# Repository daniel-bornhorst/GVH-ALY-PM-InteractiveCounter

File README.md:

# GVH-ALY-PM-InteractiveCounter

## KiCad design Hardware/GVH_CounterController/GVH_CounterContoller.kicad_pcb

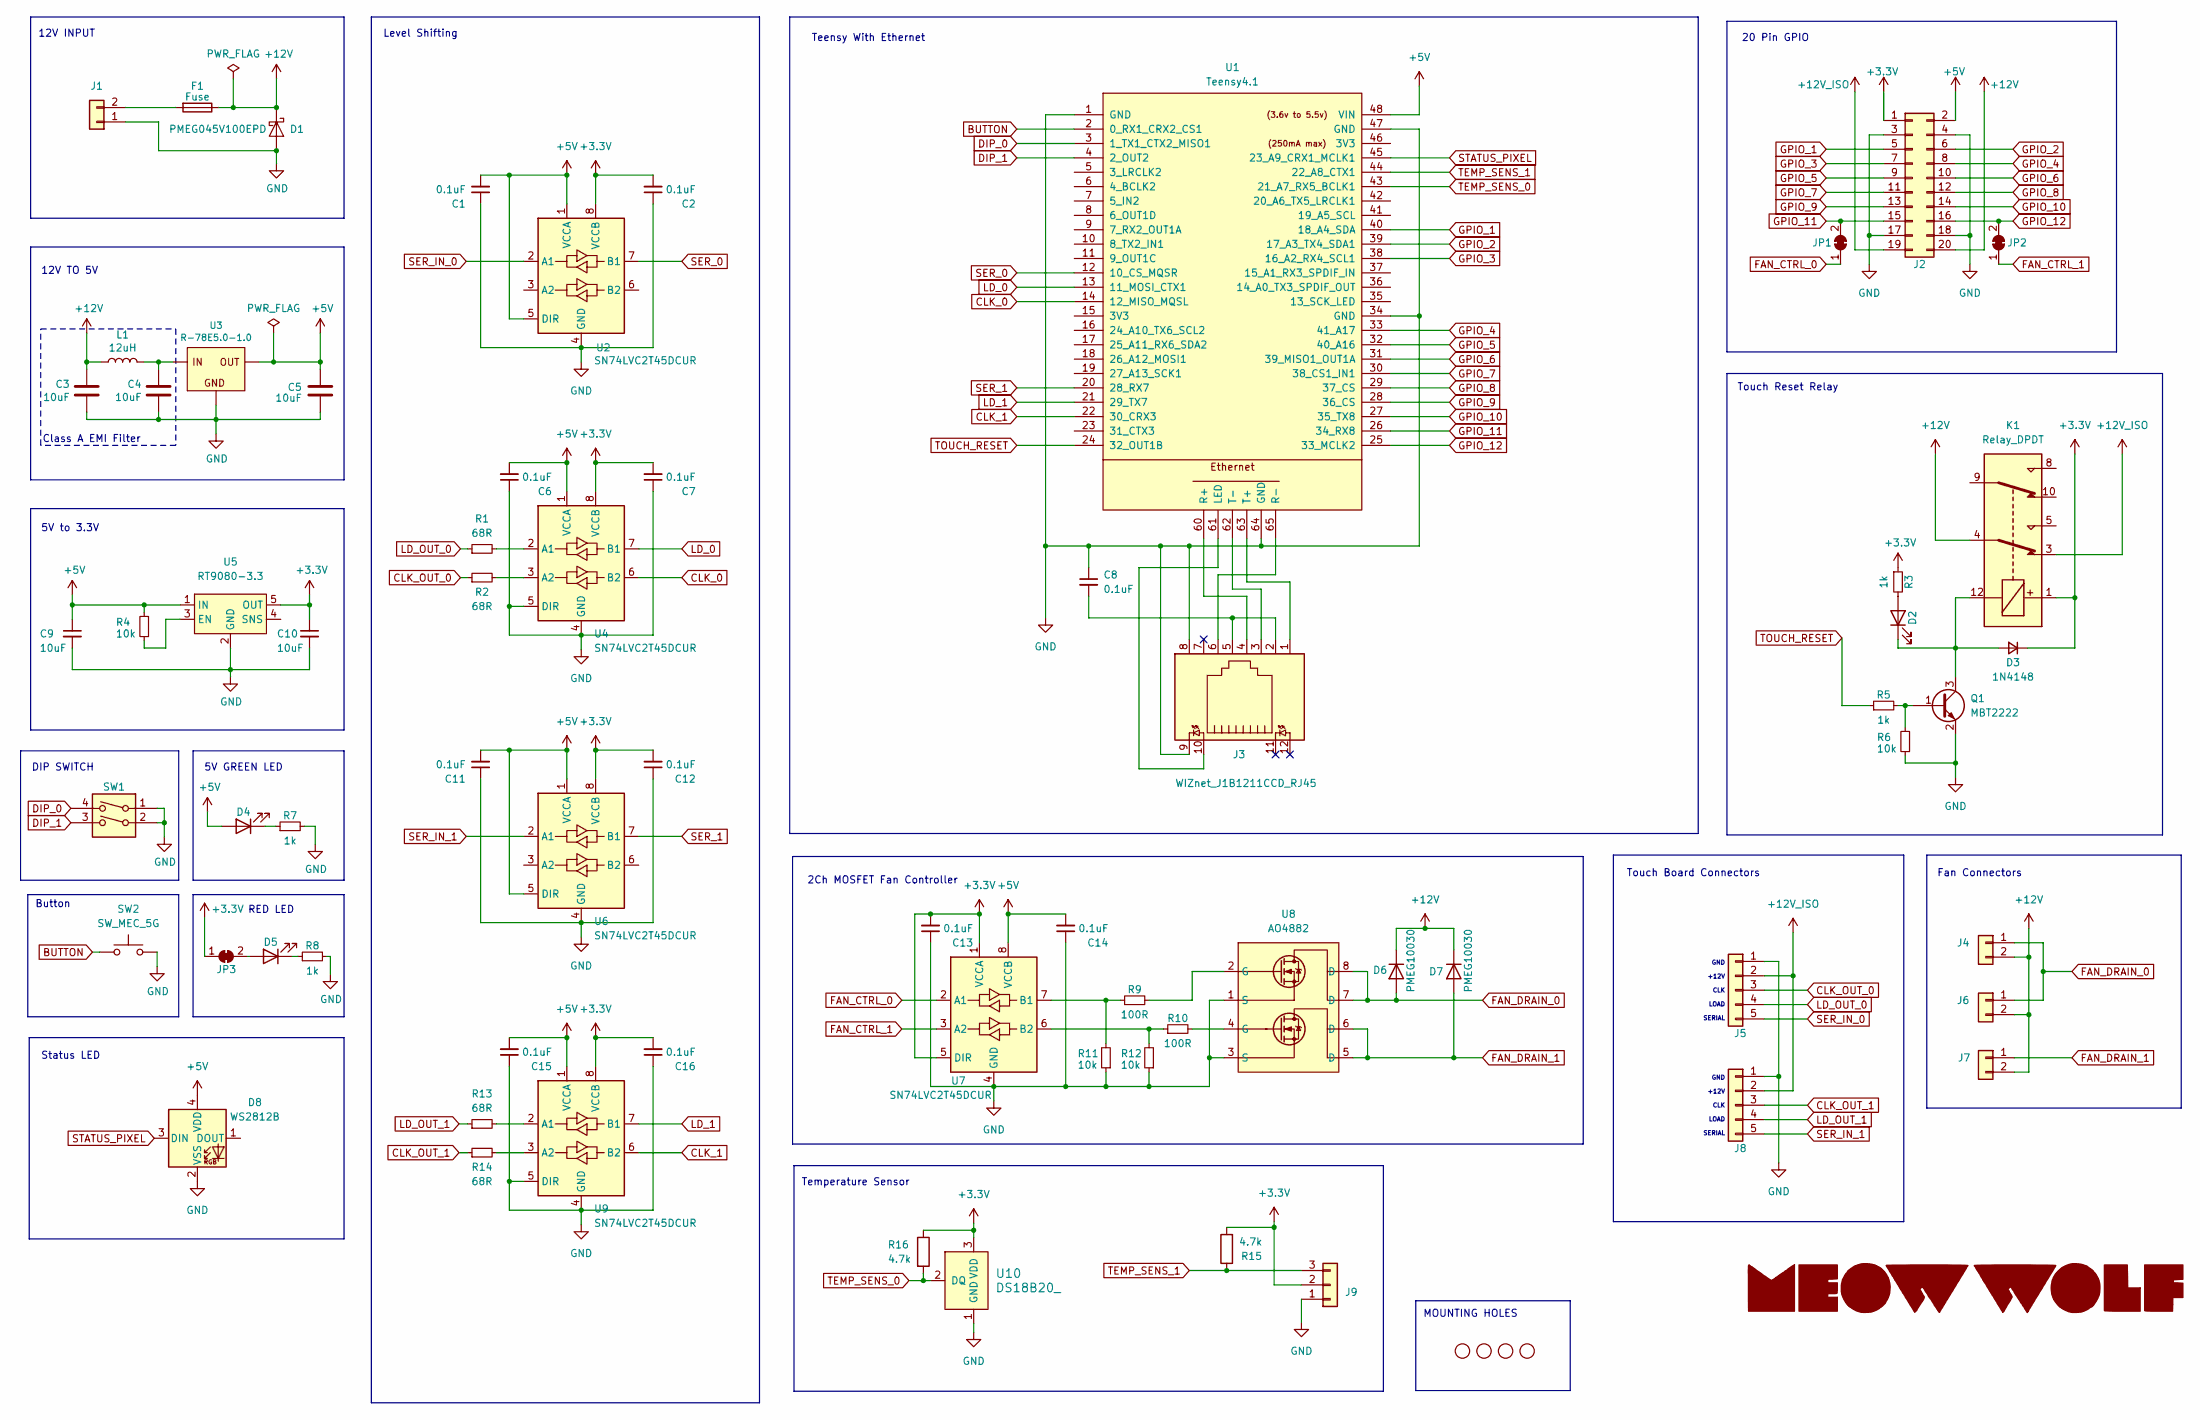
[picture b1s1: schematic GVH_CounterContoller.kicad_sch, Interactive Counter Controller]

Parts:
C1, C2, C6, C7, C11, C12, C13, C14, C15, C16: 0.1uF; C_0402_1005Metric; LCSC C1525
C3, C4, C5: 10uF; C_1206_3216Metric; Digikey P/N 1276-6767-1-ND
C8: 0.1uF; C_0805_2012Metric; LCSC C1711
C9, C10: 10uF; C_0805_2012Metric; LCSC C15850
D1: PMEG045V100EPD; Nexperia_CFP15_SOT-1289; LCSC C5183016
D2, D5: RED LED; LED_0603_1608Metric; Digikey P/N LTST-C190KRKT
D3: 1N4148; D_SOD-323; Digikey P/N 1N4148WS-FDICT-ND
D4: GREEN LED; LED_0603_1608Metric; Digikey P/N 160-1888-1-ND
D6, D7: PMEG10030; D_SOD-128; LCSC C5260346
D8: WS2812B; LED_WS2812B-2020_PLCC4_2.0x2.0mm; LCSC C965555
F1: Fuse; Fuseholder_2AG_5x15mm_Littelfuse_01110501Z; Digikey P/N F4189-ND
H1, H2, H3, H4: STAND-OFF
J1: Molex Ultra-Fit; MOLEX_ULTRAFIT-RA-2POS_1723104102; Digikey P/N 900-1723104102-ND
J2: Vertical Header Pins; PinHeader_2x10_P2.54mm_Vertical; Digikey P/N 2057-PH2-20-UA-ND
J3: WIZnet_J1B1211CCD_RJ45; Digikey P/N 1278-1052-ND
J4, J6, J7: Molex Micro-Fit; MOLEX_MICROFIT-VERT-2POS_436500215; Digikey P/N WM1917-ND
J5, J8: Molex Micro-Fit; MOLEX_MICROFIT-RA-5POS_436500500; Digikey P/N WM1863-ND
J9: Molex Micro-Fit; MOLEX_MICROFIT-RA-3POS_436500300; Digikey P/N WM1918-ND
JP1, JP2, JP3: SolderJumper_2_Bridged; SolderJumper-2_P1.3mm_Bridged_RoundedPad1.0x1.5mm
K1: Relay_DPDT; Relay_DPDT_Kemet_EC2; Digikey P/N 399-11042-5-ND
L1: 12uH; L_Changjiang_FNR4030S; LCSC C167880
LOGO1: MeowWolf_Logo_Horizontal
Q1: MBT2222; SOT-23-3; LCSC C82460
R1, R2, R13, R14: 68R; R_0402_1005Metric; LCSC C25131
R3, R5, R7, R8: 1k; R_0603_1608Metric; Digikey P/N 311-1.00KHRCT-ND
R4, R6, R11, R12: 10k; R_0603_1608Metric; LCSC C98220
R9, R10: 100R; R_0603_1608Metric; Digikey P/N 311-100HRCT-ND
R15, R16: 4.7k; R_0603_1608Metric; LCSC C99782
SW1: SW_DIP_x02; SW_DIP_SPSTx02_Slide_KingTek_DSHP02TS_W7.62mm_P1.27mm; LCSC C7462922
SW2: SW_MEC_5G; SW_TH_Tactile_Omron_B3F-10xx; Digikey P/N SW402-ND
U1: Teensy4.1; Teensy41_ethernet_only; Digikey P/N 1568-DEV-16996-ND
U2, U4, U6, U7, U9: SN74LVC2T45DCUR; VSSOP-8_2.4x2.1mm_P0.5mm; Digikey P/N 296-32331-1-ND
U3: R-78E5.0-1.0; DC-DC_CONVERTER_R-78E5; Digikey P/N 945-2201-ND
U5: RT9080-3.3; SOT-23-5; LCSC C841192
U8: AO4882; SOIC-8_3.9x4.9mm_P1.27mm; Digikey P/N 785-1317-1-ND
U10: DS18B20_; TO-92-3; Digikey P/N DS18B20+-ND

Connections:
+3.3V: C2.2, C7.2, C10.1, C12.2, C13.2, C16.2, D3.1 (K), J2.1, J9.2, JP3.1 (A), K1.1, R3.1, R15.2, R16.1, U2.8 (VCCB), U4.8 (VCCB), U5.5 (OUT), U6.8 (VCCB), U7.1 (VCCA), U7.5 (DIR), U9.8 (VCCB), U10.3 (VDD)
+5V: C1.2, C5.1, C6.2, C9.1, C11.2, C14.2, C15.2, D4.2 (A), D8.4 (VDD), J2.2, R4.2, U1.48 (VIN), U2.1 (VCCA), U2.5 (DIR), U3.VOUT (OUT), U4.1 (VCCA), U5.1 (IN), U6.1 (VCCA), U6.5 (DIR), U7.8 (VCCB), U9.1 (VCCA)
+12V: C3.1, D1.3 (K), D6.1 (K), D7.1 (K), F1.1, J2.20, J4.2, J6.2, J7.2, K1.4, L1.1
+12V_ISO: J2.19, J5.2, J8.2, K1.3
BUTTON: SW2.1 (A), U1.2 (0_RX1_CRX2_CS1)
CLK_0: U1.14 (12_MISO_MQSL), U4.6 (B2)
CLK_1: U1.22 (30_CRX3), U9.6 (B2)
CLK_OUT_0: J5.3, R2.1
CLK_OUT_1: J8.3, R14.1
DIP_0: SW1.4, U1.3 (1_TX1_CTX2_MISO1)
DIP_1: SW1.3, U1.4 (2_OUT2)
FAN_CTRL_0: JP1.1 (A), U7.2 (A1)
FAN_CTRL_1: JP2.1 (A), U7.3 (A2)
FAN_DRAIN_0: D6.2 (A), J4.1, J6.1, U8.7 (D), U8.8 (D)
FAN_DRAIN_1: D7.2 (A), J7.1, U8.5 (D), U8.6 (D)
GND: C1.1, C2.1, C3.2, C4.2, C5.2, C6.1, C7.1, C8.1, C9.2, C10.2, C11.1, C12.1, C13.1, C14.1, C15.1, C16.1, D1.1 (A), D1.2 (A), D8.2 (VSS), J1.1, J2.3, J2.4, J2.17, J2.18, J3.8, J3.9, J5.1, J8.1, J9.1, Q1.2 (E), R6.1, R7.2, R8.2, R11.1, R12.1, SW1.1, SW1.2, SW2.2 (B), U1.1 (GND), U1.34 (GND), U1.47 (GND), U1.64 (GND), U2.4 (GND), U3.GND, U4.4 (GND), U4.5 (DIR), U5.2 (GND), U6.4 (GND), U7.4 (GND), U8.1 (S), U8.3 (S), U9.4 (GND), U9.5 (DIR), U10.1 (GND)
GPIO_1: J2.5, U1.40 (18_A4_SDA)
GPIO_2: J2.6, U1.39 (17_A3_TX4_SDA1)
GPIO_3: J2.7, U1.38 (16_A2_RX4_SCL1)
GPIO_4: J2.8, U1.33 (41_A17)
GPIO_5: J2.9, U1.32 (40_A16)
GPIO_6: J2.10, U1.31 (39_MISO1_OUT1A)
GPIO_7: J2.11, U1.30 (38_CS1_IN1)
GPIO_8: J2.12, U1.29 (37_CS)
GPIO_9: J2.13, U1.28 (36_CS)
GPIO_10: J2.14, U1.27 (35_TX8)
GPIO_11: J2.15, JP1.2 (B), U1.26 (34_RX8)
GPIO_12: J2.16, JP2.2 (B), U1.25 (33_MCLK2)
LD_0: U1.13 (11_MOSI_CTX1), U4.7 (B1)
LD_1: U1.21 (29_TX7), U9.7 (B1)
LD_OUT_0: J5.4, R1.1
LD_OUT_1: J8.4, R13.1
unnamed: C8.2, J3.2, J3.5
unnamed: D2.2 (A), R3.2
unnamed: D2.1 (K), D3.2 (A), K1.12, Q1.3 (C)
unnamed: D4.1 (K), R7.1
unnamed: D5.2 (A), JP3.2 (B)
unnamed: D5.1 (K), R8.1
unnamed: F1.2, J1.2
unnamed: Q1.1 (B), R5.2, R6.2
unnamed: R9.2, U8.2 (G)
unnamed: R10.2, U8.4 (G)
unnamed: J3.10, U1.61 (LED)
unnamed: J3.4, U1.60 (R+)
unnamed: J3.6, U1.65 (R-)
unnamed: J3.1, U1.63 (T+)
unnamed: J3.3, U1.62 (T-)
unnamed: C4.1, L1.2, U3.VIN (IN)
unnamed: R1.2, U4.2 (A1)
unnamed: R2.2, U4.3 (A2)
unnamed: R4.1, U5.3 (EN)
unnamed: R9.1, R11.2, U7.7 (B1)
unnamed: R10.1, R12.2, U7.6 (B2)
unnamed: R13.2, U9.2 (A1)
unnamed: R14.2, U9.3 (A2)
SER_0: U1.12 (10_CS_MQSR), U2.7 (B1)
SER_1: U1.20 (28_RX7), U6.7 (B1)
SER_IN_0: J5.5, U2.2 (A1)
SER_IN_1: J8.5, U6.2 (A1)
STATUS_PIXEL: D8.3 (DIN), U1.45 (23_A9_CRX1_MCLK1)
TEMP_SENS_0: R16.2, U1.43 (21_A7_RX5_BCLK1), U10.2 (DQ)
TEMP_SENS_1: J9.3, R15.1, U1.44 (22_A8_CTX1)
TOUCH_RESET: R5.1, U1.24 (32_OUT1B)

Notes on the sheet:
5V to 3.3V
Temperature Sensor
GND +12V CLK LOAD SERIAL
5V GREEN LED
12V INPUT
Teensy With Ethernet
MOUNTING HOLES
Button
DIP SWITCH
Touch Reset Relay
2Ch MOSFET Fan Controller
Level Shifting
Fan Connectors
20 Pin GPIO
Touch Board Connectors
Class A EMI Filter
Status LED
12V TO 5V
RED LED

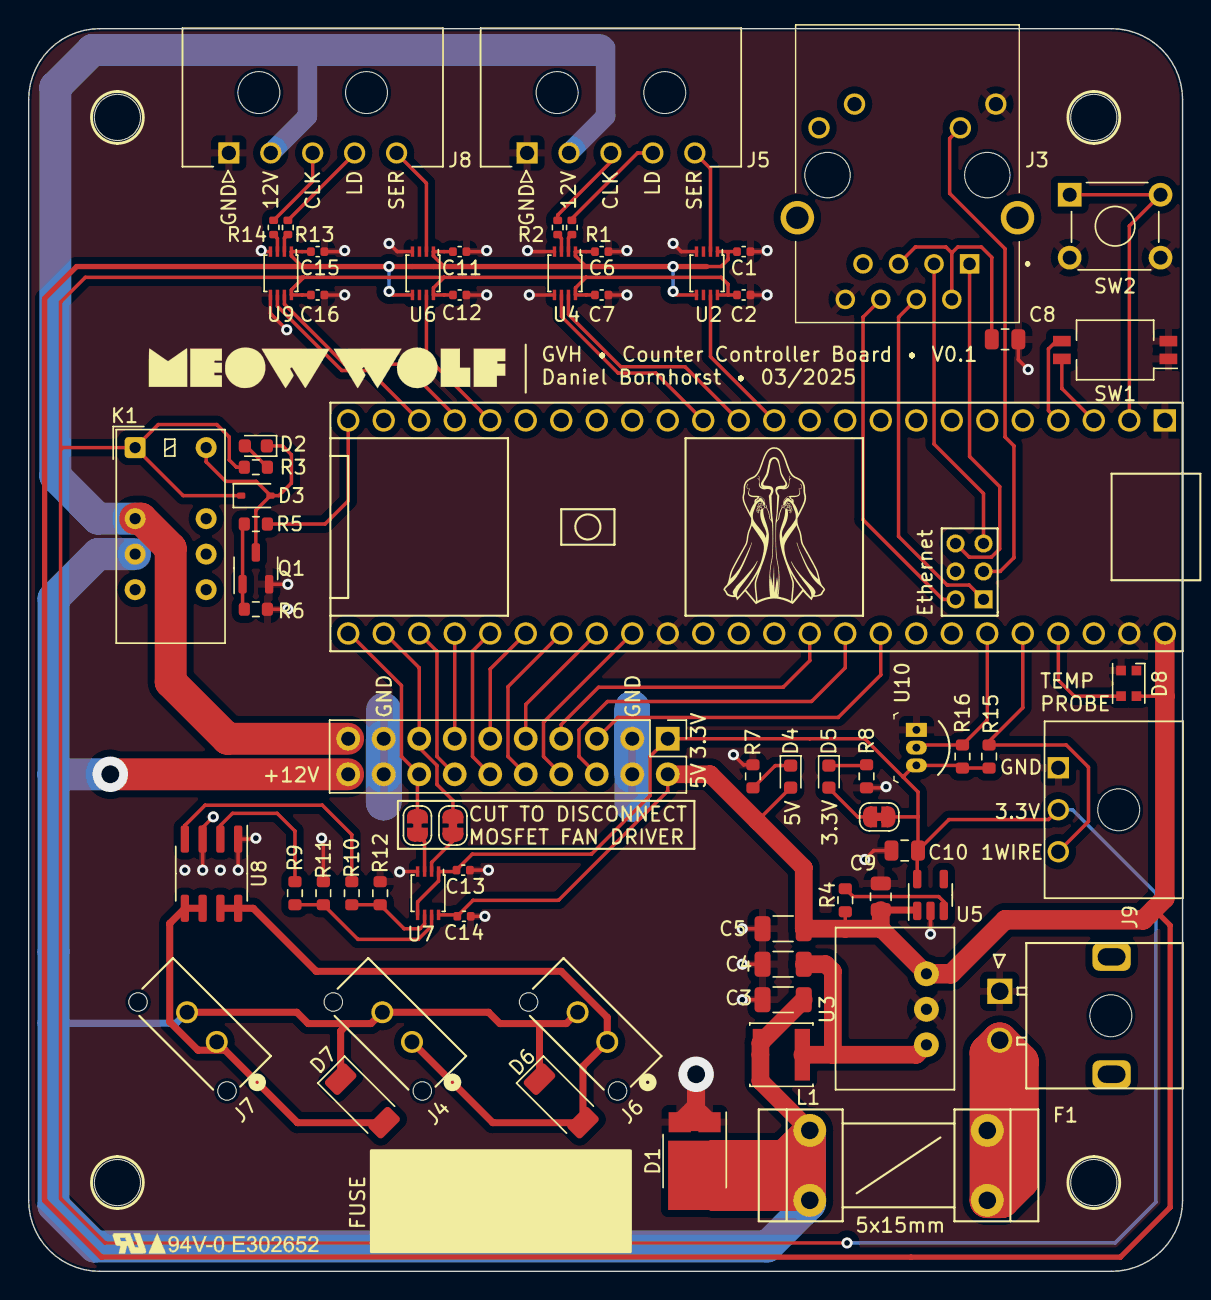
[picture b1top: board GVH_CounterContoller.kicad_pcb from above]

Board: 2 copper layers, 82.5 x 88.9 mm, 72 parts (0 on the bottom side), 63 nets.

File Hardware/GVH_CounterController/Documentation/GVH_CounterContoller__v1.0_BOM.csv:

"Reference","Value","Description","Digikey P/N","Digikey Page","LCSC","Manu #","Manu.","Package","Qty"
"C1, C2, C6, C7, C11-C16","0.1uF","100nF 16V X7R ±10% 0402 Multilayer Ceramic Capacitors","1276-1001-1-ND","https://www.digikey.com/en/products/detail/samsung-electro-m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","C1525","CL05B104KO5NNNC","Samsung Electro-Mechanics","0402 ","10"
"C3-C5","10uF","10uF ±10% 50V Ceramic Capacitor X7R 1206 (3216 Metric)","1276-6767-1-ND","https://www.digikey.com/en/products/detail/samsung-electro-m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","C89632","CL31B106KBHNNNE","Samsung Electro-Mechanics","1206","3"
"C8","0.1uF","0.1uF ±10% 50V Ceramic Capacitor X7R 0805 (2012 Metric)","1276-1003-1-ND","https://www.digikey.com/en/products/detail/samsung-electro-m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","C1711","CL21B104KBCNNNC","Samsung Electro-Mechanics","0805","1"
"C9, C10","10uF","25V 10uF X5R ±10% 0805 Multilayer Ceramic Capacitors","1276-2891-1-ND","https://www.digikey.com/en/products/detail/samsung-electro-m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","C15850","CL21A106KAYNNNE","Samsung Electro-Mechanics","0805","2"
"D1","PMEG045V100EPD","DIODE SCHOTTKY 45V 10A CFP15","1727-1904-1-ND","https://www.digikey.com/en/products/detail/nexperia-usa-inc/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","C5183016","PMEG045V100EPDZ","Nexperia USA Inc.","CFP-15","1"
"D2, D5","RED LED","Red 631nm LED Indication - 2V 0603","LTST-C190KRKT","https://www.digikey.com/en/products/detail/liteon/LTST-C190K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","C94869","LTST-C190KRKT","Lite-On","0603","2"
"D3","1N4148","Diode 75 V 150mA Surface Mount SOD-323","1N4148WS-FDICT-ND","https://www.digikey.com/en/products/detail/diodes-incorporat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","C2128","1N4148WS","Jiangsu Changjing Electronics Technology Co., Ltd.","SOD-323","1"
"D4","GREEN LED","Green 525nm LED Indication - 3.2V 0603","160-1888-1-ND","https://www.digikey.com/en/products/detail/liteon/LTST-C191T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","C125101","LTST-C191TGKT","Lite-On","0603","1"
"D6, D7","PMEG10030","DIODE SCHOTT 100V 3A SOD128/CFP5","1727-2397-1-ND","https://www.digikey.com/en/products/detail/nexperia-usa-inc/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","C5260346","PMEG10030ELPX","Nexperia USA Inc.","SOD-128","2"
"D8","WS2812B","2020 WS2812B Adressable RGB LED","1528-4684-ND","https://www.digikey.com/en/products/detail/adafruit-industri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","C965555","WS2812B-2020","Worldsemi","SMD,2x2mm","1"
"F1","Fuse","Fuse Holder","F4189-ND","https://www.digikey.com/en/products/detail/littelfuse-inc/01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","-","01110501Z","Littelfuse Inc.","THT","1"
"H1-H4","STAND-OFF","","-","-","-","","-","-","4"
"J1","Molex Ultra-Fit","Connector Header Through Hole, Right Angle 2 position 0.138"" (3.50mm)","900-1723104102-ND","https://www.digikey.com/en/products/detail/molex/1723104102/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","-","1723104102","MOLEX","THT","1"
"J2","Vertical Header Pins","Connector Header Through Hole 20 position 2 rows 0.100"" (2.54mm)","2057-PH2-20-UA-ND","https://www.digikey.com/en/products/detail/adam-tech/PH2-20-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","-","PH2-20-UA","Adam Tech","THT","1"
"J3","WIZnet_J1B1211CCD_RJ45","1 Port RJ45Through Hole 10/100 Base-T, AutoMDIX","1278-1052-ND","https://www.digikey.com/en/products/detail/wiznet/J1B1211CCD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","-","J1B1211CCD","WIZnet","THT","1"
"J4, J6, J7","Molex Micro-Fit","CONN HEADER VERTICAL 2POS 3MM","WM1917-ND","https://www.digikey.com/en/products/detail/molex/0436500215/283461","-","0436500215","MOLEX","THT","3"
"J5, J8","Molex Micro-Fit","CONN HEADER VERTICAL 4POS 3MM","WM1863-ND","https://www.digikey.com/en/products/detail/molex/0436500500/268992","-","0436500500","MOLEX","THT","2"
"J9","Molex Micro-Fit","CONN HEADER RIGHT ANGLE 3POS 3MM","WM1918-ND","https://www.digikey.com/en/products/detail/molex/0436500315/283462","-","0436500315","MOLEX","THT","1"
"JP1-JP3","SolderJumper_2_Bridged","","","","","","","","3"
"K1","Relay_DPDT","RELAY GENERAL PURPOSE DPDT 2A 3V","399-11042-5-ND","https://www.digikey.com/en/products/detail/kemet/EC2-3NU/4291108","-","EC2-3NU","KEMET","THT","1"
"L1","12uH","1.4A 12uH SMD 4x4mm Power Inductor","535-ASPI-4030S-120M-TCT-ND","https://www.digikey.com/en/products/detail/abracon-llc/ASPI-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","C167880","FNR4030S120MT","Changjiang Microelectronics Tech","SMD,4x4mm","1"
"LOGO1","MeowWolf_Logo_Horizontal","","-","-","-","-","-","-","1"
"Q1","MBT2222","40V 225mW 100@150mA,10V 600mA NPN SOT-23 Bipolar (BJT)","MMBT2222ALT1GOSCT-ND","https://www.digikey.com/en/products/detail/onsemi/MMBT2222AL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","C82460","MMBT2222ALT1G","onsemi","SOT-23","1"
"R1, R2, R13, R14","68R","68 Ohms ±1% 1/10W Chip Resistor 0402","P68.0LCT-ND","https://www.digikey.com/en/products/detail/panasonic-electro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","C25131","ERJ-2RKF68R0X","Panasonic Electronic Components","-- mixed values --","4"
"R3, R5, R7, R8","1k","100mW Thick Film Resistors 75V ±100ppm/℃ ±1% 1kΩ 0603 Chip Resistor","311-1.00KHRCT-ND","https://www.digikey.com/en/products/detail/yageo/RC0603FR-07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","C22548","RC0603FR-071KL","YAGEO","0603","4"
"R4, R6, R11, R12","10k","100mW Thick Film Resistors 75V ±100ppm/℃ ±1% 10kΩ 0603 Chip Resistor","311-10.0KHRCT-ND","https://www.digikey.com/en/products/detail/yageo/RC0603FR-07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","C98220","RC0603FR-0710KL","YAGEO","0603","4"
"R9, R10","100R","100mW Thick Film Resistors 75V ±100ppm/℃ ±1% 100Ω 0603 Chip Resistor","311-100HRCT-ND","https://www.digikey.com/en/products/detail/yageo/RC0603FR-07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","C105588","RC0603FR-07100RL","YAGEO","0603","2"
"R15, R16","4.7k","100mW Thick Film Resistors 75V ±100ppm/℃ ±1% 4.7kΩ 0603 Chip Resistor","311-4.70KHRCT-ND","https://www.digikey.com/en/products/detail/yageo/RC0603FR-07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","C99782","RC0603FR-074K7L","YAGEO","0603","2"
"SW1","SW_DIP_x02","Dip Switch SPST 2 Position Surface Mount Slide (Standard) Actuator 100mA 6VDC","563-1006-1-ND","https://www.digikey.com/en/products/detail/nidec-components-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","C7462922","CHS-02TB","Nidec Components Corporation","SMD-4P","1"
"SW2","SW_MEC_5G","Tactile Switch SPST-NO Top Actuated Through Hole","SW402-ND","https://www.digikey.com/en/products/detail/omron-electronics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","-","B3F-1020","Omron Electronics Inc-EMC Div","","1"
"U1, U4, U6, U7, U9","SN74LVC2T45DCUR","Voltage Level Translator Bidirectional 1 Circuit 2 Channel 420Mbps 8-VSSOP","296-32331-1-ND","https://www.digikey.com/en/products/detail/texas-instruments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","C15741","SN74LVC2T45DCUT","Texas Instruments","VSSOP-8_P0.5mm","5"
"U2","Teensy4.1","Teensy 4.1 - ARM® Cortex®-M7 MCU 32-Bit Embedded Microcontroller w/ Etherner","1568-DEV-16996-ND","https://www.digikey.com/en/products/detail/sparkfun-electron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","","Teensy4.1","PJRC","THT","1"
"U3","R-78E5.0-1.0","Non-Isolated DC/DC Converters 6.5-32Vin 5Vout 1A SIP3","945-2201-ND","https://www.digikey.com/en/products/detail/recom-power/R-78E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","-","R-78E5.0-1.0","RECOM Power","SIP-3","1"
"U5","RT9080-3.3","Linear Voltage Regulator IC Positive Fixed 1 Output 600mA TSOT-23-5","1028-1509-1-ND","https://www.digikey.com/en/products/detail/richtek-usa-inc/R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","C841192","RT9080-33GJ5","Richtek USA Inc.","SOT-23-5","1"
"U8","AO4882","MOSFET 2N-CH 40V 8A 8SOIC","785-1317-1-ND","https://www.digikey.com/en/products/detail/alpha-omega-semic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","C477943","AO4882","Alpha & Omega Semiconductor","SOIC-8","1"
"U10","DS18B20_","1-Wire Temperature Sensor","DS18B20+-ND","https://www.digikey.com/en/products/detail/analog-devices-in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","-","DS18B20+","Maxim Integrated","TO92-3","1"

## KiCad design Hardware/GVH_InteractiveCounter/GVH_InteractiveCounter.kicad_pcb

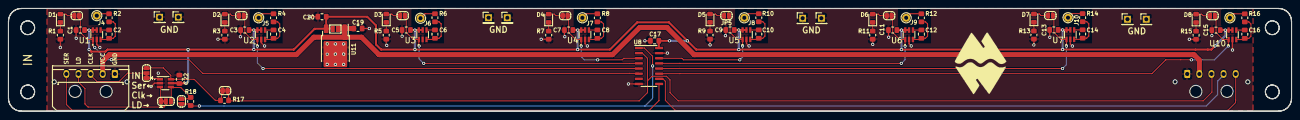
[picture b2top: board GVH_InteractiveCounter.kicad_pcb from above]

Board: 2 copper layers, 317.5 x 25.4 mm, 88 parts (1 on the bottom side), 61 nets.

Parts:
C1, C3, C5, C7, C9, C11, C13, C15, C17, C20, C22: 0.1uF; C_0805_2012Metric_Pad1.18x1.45mm_HandSolder
C2, C4, C6, C8, C10, C12, C14, C16: 22nF; C_0805_2012Metric_Pad1.18x1.45mm_HandSolder
C19: 0.33uF; C_0805_2012Metric_Pad1.18x1.45mm_HandSolder
D1, D2, D3, D4, D5, D6, D7, D8: Touch_Indicator; LED_0805_2012Metric_Pad1.15x1.40mm_HandSolder
J1, J2: Molex Micro-Fit; Molex_Micro-Fit_3.0_1x05_Horizontal_Vertical_Combo
J4, J5, J6, J7, J8, J9, J10, J11: Electrode; Pin_D1.0mm_L10.0mm
J12, J13, J14, J15, J16, J17, J18, J19: Conn_01x01; PinHeader_1x01_P2.54mm_Vertical
JP1, JP2, JP3, JP4, JP5, JP6, JP7, JP8: SolderJumper_2_Bridged; SolderJumper-2_P1.3mm_Open_RoundedPad1.0x1.5mm
JP11: SolderJumper_2_Open; SolderJumper-2_P1.3mm_Open_Pad1.0x1.5mm
JP14, JP15: SolderJumper_3_Bridged12; SolderJumper-3_P1.3mm_Bridged12_RoundedPad1.0x1.5mm
JP16, JP17: SolderJumper_2_Open; SolderJumper-2_P1.3mm_Open_RoundedPad1.0x1.5mm
R1, R3, R5, R7, R9, R11, R13, R15: 150R; R_0805_2012Metric_Pad1.20x1.40mm_HandSolder
R2, R4, R6, R8, R10, R12, R14, R16: 10K; R_0805_2012Metric_Pad1.20x1.40mm_HandSolder
R17, R18: 100; R_0805_2012Metric_Pad1.20x1.40mm_HandSolder
U1, U2, U3, U4, U5, U6, U7, U10: AT42QT1010; AT42QT1010-TSGR_1
U8: SN74HC165DR; SOP-16_3.9x9.9mm_P1.27mm
U11: L7805; TO-252-2
U13: SN74LVC2G17; SOT-23-6_Handsoldering

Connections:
+5V: C1.1, C3.1, C5.1, C7.1, C9.1, C11.1, C13.1, C15.1, C17.1, C20.1, C22.1, JP11.2 (B), U1.5 (VDD), U1.6 (SYNC), U2.5 (VDD), U2.6 (SYNC), U3.5 (VDD), U3.6 (SYNC), U4.5 (VDD), U4.6 (SYNC), U5.5 (VDD), U5.6 (SYNC), U6.5 (VDD), U6.6 (SYNC), U7.5 (VDD), U7.6 (SYNC), U8.16 (VCC), U10.5 (VDD), U10.6 (SYNC), U11.3 (OUT), U13.5 (VCC)
/Touch Sensor 1/TOUCH_PAD: J4.1, R2.1
/Touch Sensor 2/TOUCH_PAD: J5.1, R4.1
/Touch Sensor 3/TOUCH_PAD: J6.1, R6.1
/Touch Sensor 4/TOUCH_PAD: J7.1, R8.1
/Touch Sensor 5/TOUCH_PAD: J8.1, R10.1
/Touch Sensor 6/TOUCH_PAD: J9.1, R12.1
/Touch Sensor 7/TOUCH_PAD: J10.1, R14.1
/Touch Sensor 8/TOUCH_PAD: J11.1, R16.1
CLK: J1.3, JP14.2 (C)
CLK_OUT: J2.3, JP16.2 (B), R17.1, U8.2 (CLK)
GND: C1.2, C3.2, C5.2, C7.2, C9.2, C11.2, C13.2, C15.2, C17.2, C19.2, C20.2, C22.2, J1.1, J2.1, J12.1, J13.1, J14.1, J15.1, J16.1, J17.1, J18.1, J19.1, R1.1, R3.1, R5.1, R7.1, R9.1, R11.1, R13.1, R15.1, U1.2 (VSS), U2.2 (VSS), U3.2 (VSS), U4.2 (VSS), U5.2 (VSS), U6.2 (VSS), U7.2 (VSS), U8.8 (GND), U8.15 (~CE), U10.2 (VSS), U11.2 (GND), U13.2 (GND)
LOAD_OUT: J2.4, JP17.2 (B), R18.1, U8.1 (~LD)
unnamed: D1.2 (A), JP1.2 (B)
unnamed: D1.1 (K), R1.2
unnamed: D2.2 (A), JP2.2 (B)
unnamed: D2.1 (K), R3.2
unnamed: D3.2 (A), JP3.2 (B)
unnamed: D3.1 (K), R5.2
unnamed: D4.2 (A), JP4.2 (B)
unnamed: D4.1 (K), R7.2
unnamed: D5.2 (A), JP5.2 (B)
unnamed: D5.1 (K), R9.2
unnamed: D6.2 (A), JP6.2 (B)
unnamed: D6.1 (K), R11.2
unnamed: D7.2 (A), JP7.2 (B)
unnamed: D7.1 (K), R13.2
unnamed: D8.2 (A), JP8.2 (B)
unnamed: D8.1 (K), R15.2
unnamed: JP14.1 (A), U13.1 (1A)
unnamed: JP14.3 (B), JP16.1 (A), R17.2, U13.6 (1Y)
unnamed: JP15.1 (A), U13.3 (2A)
unnamed: JP15.3 (B), JP17.1 (A), R18.2, U13.4 (2Y)
unnamed: C2.2, U1.4 (SNS)
unnamed: C2.1, R2.2, U1.3 (SNSK)
unnamed: C4.2, U2.4 (SNS)
unnamed: C4.1, R4.2, U2.3 (SNSK)
unnamed: C6.2, U3.4 (SNS)
unnamed: C6.1, R6.2, U3.3 (SNSK)
unnamed: C8.2, U4.4 (SNS)
unnamed: C8.1, R8.2, U4.3 (SNSK)
unnamed: C10.2, U5.4 (SNS)
unnamed: C10.1, R10.2, U5.3 (SNSK)
unnamed: C12.2, U6.4 (SNS)
unnamed: C12.1, R12.2, U6.3 (SNSK)
unnamed: C14.2, U7.4 (SNS)
unnamed: C14.1, R14.2, U7.3 (SNSK)
unnamed: C16.2, U10.4 (SNS)
unnamed: C16.1, R16.2, U10.3 (SNSK)
SERIAL_IN: J2.5, U8.10 (SER)
SERIAL_OUT: J1.5, U8.9 (QH)
TOUCH_1: JP1.1 (A), U1.1 (OUT), U8.6 (H)
TOUCH_2: JP2.1 (A), U2.1 (OUT), U8.5 (G)
TOUCH_3: JP3.1 (A), U3.1 (OUT), U8.4 (F)
TOUCH_4: JP4.1 (A), U4.1 (OUT), U8.3 (E)
TOUCH_5: JP5.1 (A), U5.1 (OUT), U8.14 (D)
TOUCH_6: JP6.1 (A), U6.1 (OUT), U8.13 (C)
TOUCH_7: JP7.1 (A), U7.1 (OUT), U8.12 (B)
TOUCH_8: JP8.1 (A), U8.11 (A), U10.1 (OUT)
VCC: C19.1, J1.2, J2.2, JP11.1 (A), U11.1 (IN)
~LOAD: J1.4, JP15.2 (C)

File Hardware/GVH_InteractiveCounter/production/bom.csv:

Designator,Footprint,Quantity,Value,LCSC Part #
"C1, C11, C13, C15, C17, C20, C22, C3, C5, C7, C9",0805,11,0.1uF,C1711
C19,0805,1,0.33uF,C73142
"D1, D2, D3, D4, D5, D6, D7, D8",0805,8,Touch_Indicator,C2297
"R1, R11, R13, R15, R3, R5, R7, R9",0805,8,150R,C17471
"R10, R12, R14, R16, R2, R4, R6, R8",0805,8,10K,C17414
"R17, R18",0805,2,100,C17408
"U1, U10, U2, U3, U4, U5, U6, U7",SOT-23-6,8,AT42QT1010-TSHR,C74512
U11,DPAK,1,L7805,C310413
U13,SOT-23-6,1,SN74LVC2G17,C10429
U8,SOP-16,1,SN74HC165DR,C61060

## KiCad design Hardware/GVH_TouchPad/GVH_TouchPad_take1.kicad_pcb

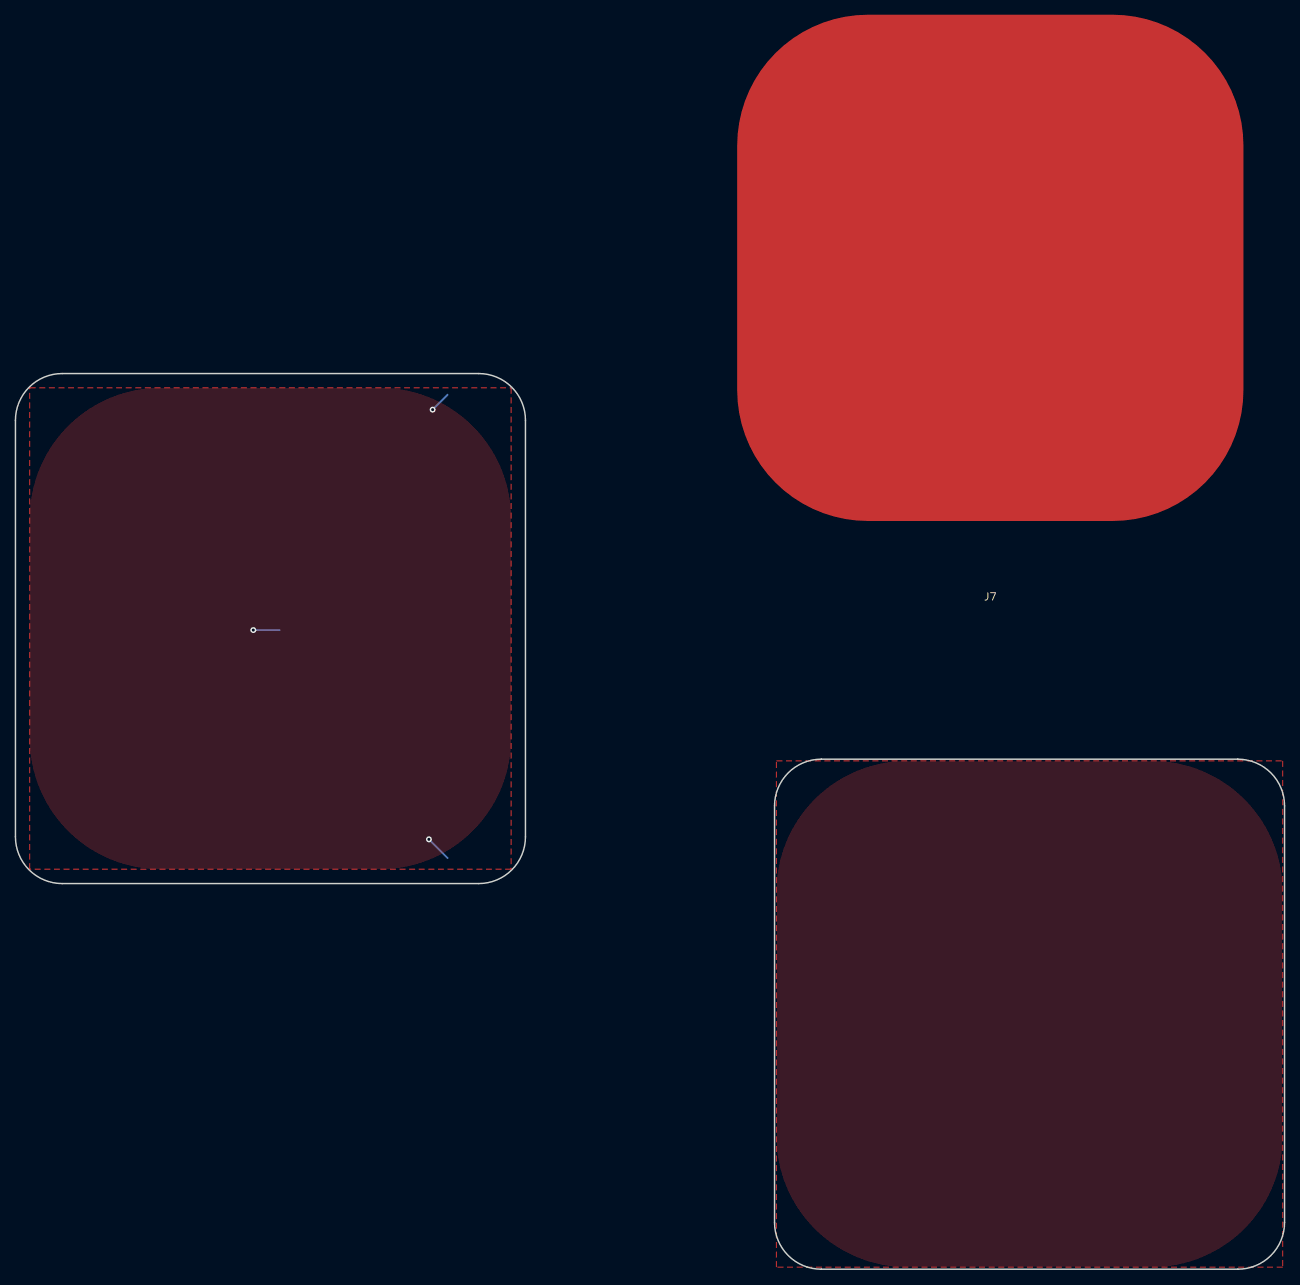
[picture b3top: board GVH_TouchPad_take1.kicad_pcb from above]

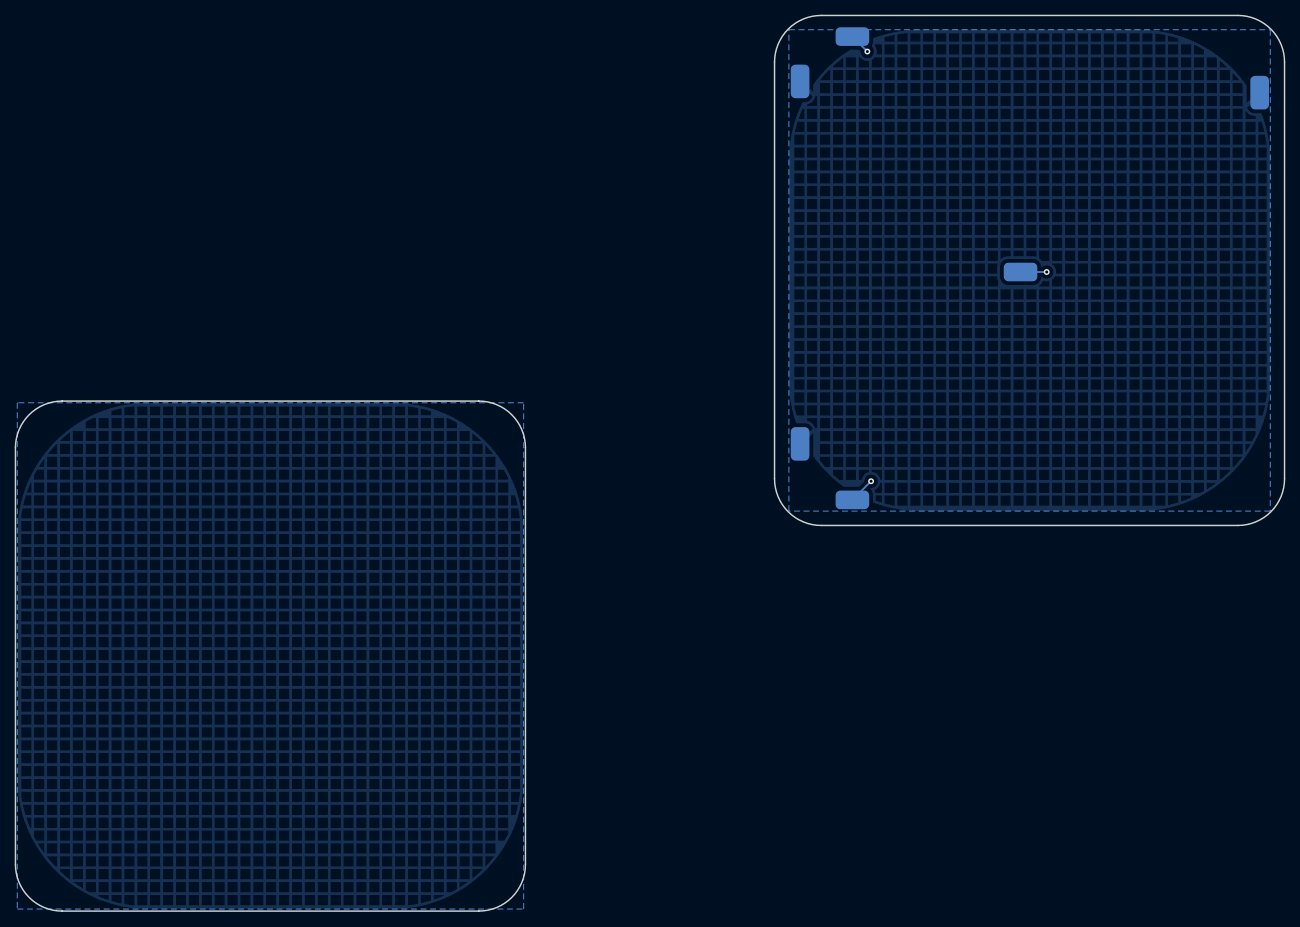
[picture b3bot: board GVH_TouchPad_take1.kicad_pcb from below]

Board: 2 copper layers, 69.3 x 69.3 mm, 7 parts (6 on the bottom side), 2 nets.

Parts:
J1, J2, J3, J4, J5, J6: Conn_01x01; SMD_Pad
J7: Conn_01x01; Large Touch Pad

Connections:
GND: J1.1, J2.1, J3.1
TOUCH: J4.1, J5.1, J6.1, J7.1

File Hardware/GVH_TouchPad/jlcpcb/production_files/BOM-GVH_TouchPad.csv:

Comment,Designator,Footprint,LCSC,Quantity
Conn_01x01,J5,SMD_Pad,,1
Conn_01x01,J4,SMD_Pad,,1
Conn_01x01,J2,SMD_Pad,,1
Conn_01x01,J1,SMD_Pad,,1

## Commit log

2024-10-18 Init
2024-10-19 All shift in working, teensy ethernet working
2024-10-19 Changed output to better show how bits correspond with touch sectors
2024-11-15 Added PCB Parts to KiCad Project Library
2024-11-18 Saving before changing from 1206 to 0805 components
2024-11-21 Backing up work on PCB before some major changes
2024-12-03 Board version 2 done. Not happy will start over
2024-12-03 Update README.md - fix spelling
2024-12-03 Created touch electrode board
2024-12-05 Finished another layout. This is probably the one.
    Also finished the touch pad layouts
2024-12-06 Updated all of the parts to have the LCSC part numbers
2024-12-07 Layouts done and ordered.
2024-12-18 Cleaned up some of the Kicad projects
2024-12-19 Untracking more files
2024-12-19 Repo cleanup
2024-12-28 Added counter controller PCB
2025-01-30 Counter Controller PCB - Added IO Level Shifter Sheet, Updated from Template
2025-01-30 Bump
2025-02-02 Added outlines for counter controller
2025-02-20 Added Mosfet fan controller to CounterController Schematic
2025-02-20 Checkpoint before rerouting the power supply
2025-02-22 Added header for two board stack design
    This will allow the fans to be connected horizontally
2025-02-22 Checkpoint before removing fan connectors
2025-02-26 Noticed that voltage translators wont work 3-5v, changing that part
2025-02-27 Level shifting redesign complete
2025-02-27 Added Glass fuse and cleaned up fan controller
2025-02-28 About to change gate driver buffer, it wont shift logic up
2025-03-07 Controller board finished and documentation created
